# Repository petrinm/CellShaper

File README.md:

# CellShaper
The ultimate 18650 battery cell tester

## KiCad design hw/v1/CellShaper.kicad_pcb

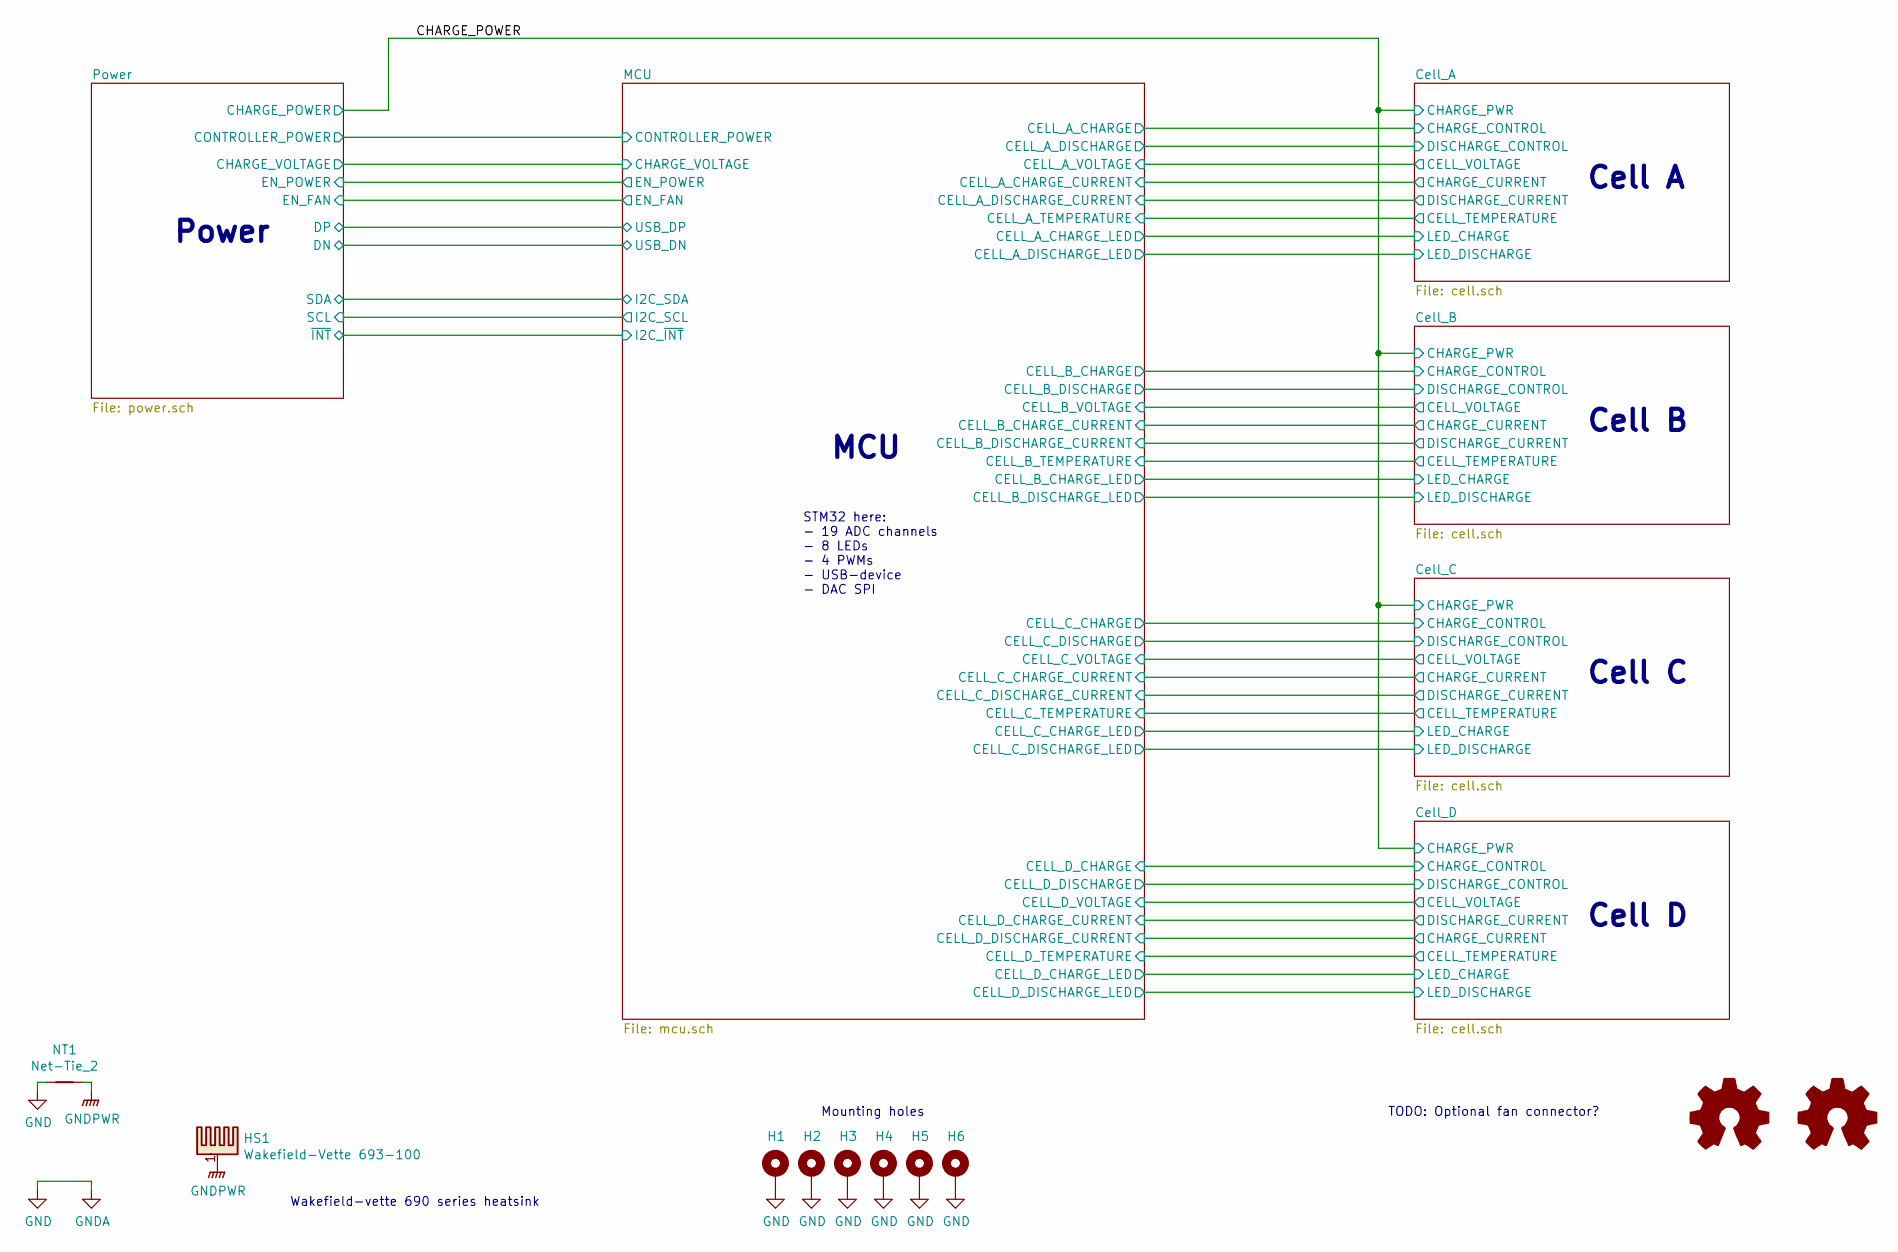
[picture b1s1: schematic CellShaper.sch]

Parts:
H1, H2, H3, H4, H5, H6: M3 hole; MountingHole_3.2mm_M3_Pad
HS1: Wakefield-Vette 693-100; Wakefield-vette_693-100
LOGO1: Logo_Open_Hardware_Small; OSHW-Logo_7.5x8mm_Copper
LOGO2: Logo_Open_Hardware_Small; OSHW-Logo_7.5x8mm_SilkScreen
NT1: Net-Tie_2; NetTie-2_SMD_Pad2.0mm

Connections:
GND: H1.1, H2.1, H3.1, H4.1, H5.1, H6.1, NT1.1; also elsewhere on the board
GNDPWR: HS1.1, NT1.2; also elsewhere on the board

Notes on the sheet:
Wakefield-vette 690 series heatsink
STM32 here: - 19 ADC channels - 8 LEDs - 4 PWMs - USB-device - DAC SPI
TODO: Optional fan connector?
Mounting holes
Cell A
Cell B
Cell D
Cell C
MCU
Power

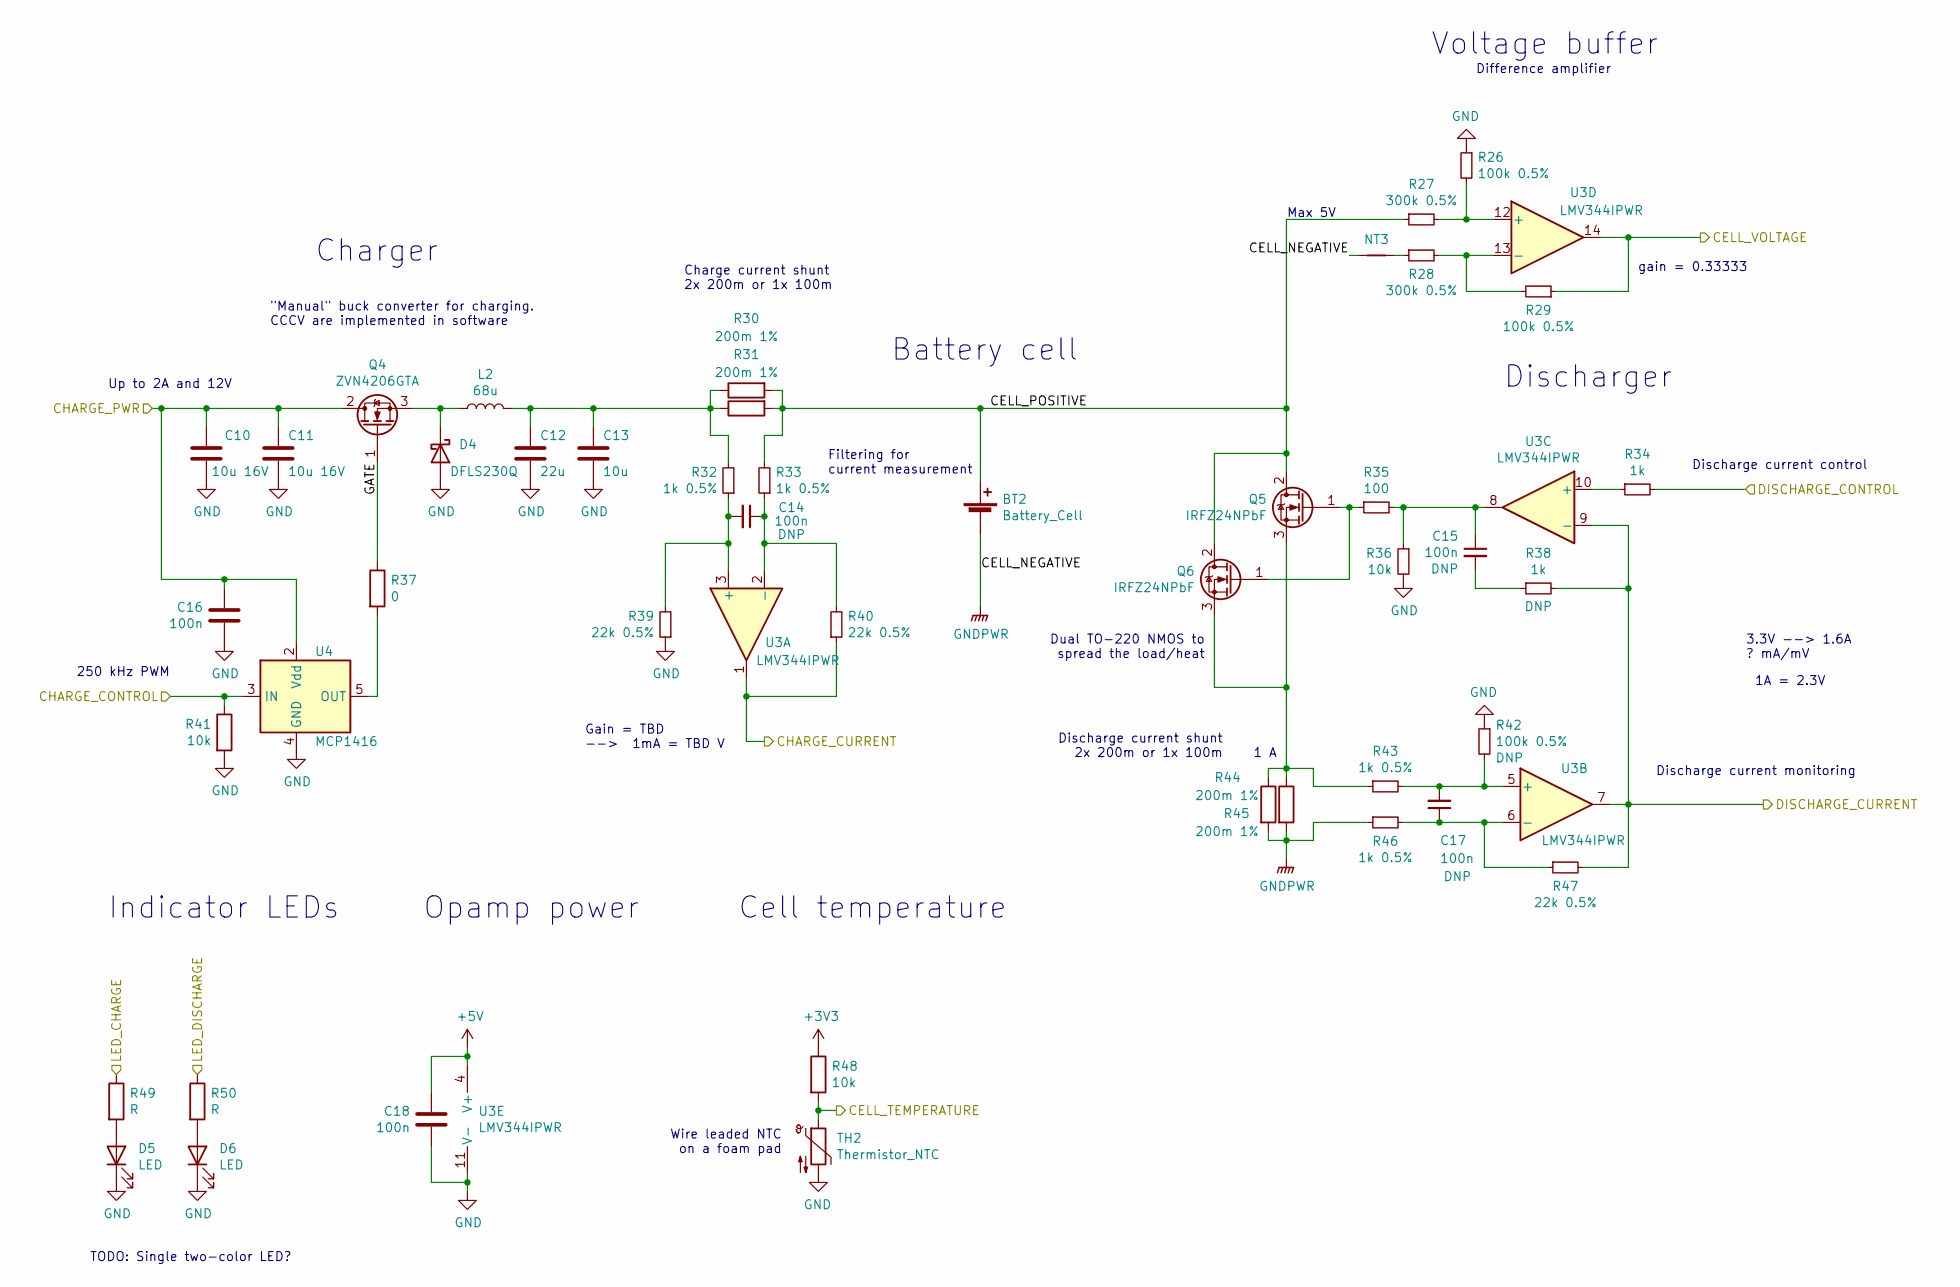
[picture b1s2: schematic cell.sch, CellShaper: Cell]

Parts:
BT1: Battery_Cell; BatteryHolder_Keystone_534_54
C1, C2: 10u 16V; C_0805_2012Metric
C3: 22u; C_0805_2012Metric
C4: 10u; C_0805_2012Metric
C5, C6, C7, C8, C9: 100n; C_0603_1608Metric
D1: DFLS230Q; D_PowerDI-123
D2, D3: LED; LED_0603_1608Metric
L1: 68u; L_Wuerth_HCM-1052
NT5: Net-Tie_2; NetTie-2_SMD_Pad0.5mm
Q1: ZVN4206GTA; SOT-223-3_TabPin2
Q2, Q3: IRFZ24NPbF; TO-220-3_Vertical
R1, R4, R17: 100k 0.5%; R_0603_1608Metric
R2, R3: 300k 0.5%; R_0603_1608Metric
R5, R6, R19, R20: 200m 1%; R_1206_3216Metric
R7, R8, R18, R21: 1k 0.5%; R_0603_1608Metric
R9, R13: 1k; R_0603_1608Metric
R10: 100; R_0603_1608Metric
R11, R16, R23: 10k; R_0603_1608Metric
R12: 0; R_0603_1608Metric
R14, R15, R22: 22k 0.5%; R_0603_1608Metric
R24, R25: R; R_0603_1608Metric
TH1: Thermistor_NTC; ContactThermistor
U1: LMV344IPWR; TSSOP-14_4.4x5mm_P0.65mm
U2: MCP1416; SOT-23-5

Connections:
+3V3: R23.1; also elsewhere on the board
+5V: C9.1, U1.4 (V+); also elsewhere on the board
/CHARGE_POWER: C1.1, C2.1, C7.1, Q1.2 (D), U2.2 (Vdd); also elsewhere on the board
/Cell_A/CELL_POSITIVE: BT1.1 (+), Q2.2 (D), Q3.2 (D), R2.1, R5.2, R6.2, R8.2
/Cell_A/GATE: Q1.1 (G), R12.1
/MCU/CELL_A_CHARGE: R16.1, U2.3 (IN); also elsewhere on the board
/MCU/CELL_A_CHARGE_CURRENT: R15.1, U1.1; also elsewhere on the board
/MCU/CELL_A_CHARGE_LED: R24.1; also elsewhere on the board
/MCU/CELL_A_DISCHARGE: R9.2; also elsewhere on the board
/MCU/CELL_A_DISCHARGE_CURRENT: R13.2, R22.2, U1.7, U1.9 (-); also elsewhere on the board
/MCU/CELL_A_DISCHARGE_LED: R25.1; also elsewhere on the board
/MCU/CELL_A_TEMPERATURE: R23.2, TH1.1; also elsewhere on the board
/MCU/CELL_A_VOLTAGE: R4.1, U1.14; also elsewhere on the board
GND: C1.2, C2.2, C3.2, C4.2, C7.2, C9.2, D1.2 (A), D2.1 (K), D3.1 (K), R1.1, R11.2, R14.1, R16.2, R17.1, TH1.2, U1.11 (V-), U2.4 (GND); also elsewhere on the board
GNDPWR: BT1.2 (-), NT5.1, R19.2, R20.2, R21.1; also elsewhere on the board
unnamed: C3.1, C4.1, L1.2, R5.1, R6.1, R7.2
unnamed: C5.1, R8.1, R15.2, U1.2 (-)
unnamed: C5.2, R7.1, R14.2, U1.3 (+)
unnamed: C6.1, R10.2, R11.1, U1.8
unnamed: C6.2, R13.1
unnamed: C8.1, R21.2, R22.1, U1.6 (-)
unnamed: C8.2, R17.2, R18.2, U1.5 (+)
unnamed: D1.1 (K), L1.1, Q1.3 (S)
unnamed: D2.2 (A), R24.2
unnamed: D3.2 (A), R25.2
unnamed: Q2.1 (G), Q3.1 (G), R10.1
unnamed: Q2.3 (S), Q3.3 (S), R18.1, R19.1, R20.1
unnamed: R1.2, R2.2, U1.12 (+)
unnamed: R3.2, R4.2, U1.13 (-)
unnamed: R9.1, U1.10 (+)
unnamed: R12.2, U2.5 (OUT)

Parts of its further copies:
BT2, BT3, BT4: Battery_Cell; BatteryHolder_Keystone_534_54
C10, C11, C19, C20, C28, C29: 10u 16V; C_0805_2012Metric
C12, C21, C30: 22u; C_0805_2012Metric
C13, C22, C31: 10u; C_0805_2012Metric
C14, C15, C16, C17, C18, C23, C24, C25, C26, C27, C32, C33, C34, C35, C36: 100n; C_0603_1608Metric
D4, D7, D10: DFLS230Q; D_PowerDI-123
D5, D6, D8, D9, D11, D12: LED; LED_0603_1608Metric
NT2, NT3, NT4: Net-Tie_2; NetTie-2_SMD_Pad0.5mm
Q4, Q7, Q10: ZVN4206GTA; SOT-223-3_TabPin2
Q5, Q6, Q8, Q9, Q11, Q12: IRFZ24NPbF; TO-220-3_Vertical
R26, R29, R42, R51, R54, R67, R76, R79, R92: 100k 0.5%; R_0603_1608Metric
R27, R28, R52, R53, R77, R78: 300k 0.5%; R_0603_1608Metric
R30, R31, R44, R45, R55, R56, R69, R70, R80, R81, R94, R95: 200m 1%; R_1206_3216Metric
R32, R33, R43, R46, R57, R58, R68, R71, R82, R83, R93, R96: 1k 0.5%; R_0603_1608Metric
R34, R38, R59, R63, R84, R88: 1k; R_0603_1608Metric
R35, R60, R85: 100; R_0603_1608Metric
R36, R41, R48, R61, R66, R73, R86, R91, R98: 10k; R_0603_1608Metric
R37, R62, R87: 0; R_0603_1608Metric
R39, R40, R47, R64, R65, R72, R89, R90, R97: 22k 0.5%; R_0603_1608Metric
R49, R50, R74, R75, R99, R100: R; R_0603_1608Metric
TH2, TH3, TH4: Thermistor_NTC; ContactThermistor
U3, U5, U7: LMV344IPWR; TSSOP-14_4.4x5mm_P0.65mm
U4, U6, U8: MCP1416; SOT-23-5

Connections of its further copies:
+3V3: R48.1, R73.1, R98.1; also elsewhere on the board
+5V: C18.1, C27.1, C36.1, U3.4 (V+), U5.4 (V+), U7.4 (V+); also elsewhere on the board
/CHARGE_POWER: C10.1, C11.1, C16.1, C19.1, C20.1, C25.1, C28.1, C29.1, C34.1, Q4.2 (D), Q7.2 (D), Q10.2 (D), U4.2 (Vdd), U6.2 (Vdd), U8.2 (Vdd); also elsewhere on the board
/Cell_B/CELL_POSITIVE: BT4.1 (+), Q11.2 (D), Q12.2 (D), R77.1, R80.2, R81.2, R83.2
/Cell_B/GATE: Q10.1 (G), R87.1
/Cell_C/CELL_POSITIVE: BT2.1 (+), Q5.2 (D), Q6.2 (D), R27.1, R30.2, R31.2, R33.2
/Cell_C/GATE: Q4.1 (G), R37.1
/Cell_D/CELL_POSITIVE: BT3.1 (+), Q8.2 (D), Q9.2 (D), R52.1, R55.2, R56.2, R58.2
/Cell_D/GATE: Q7.1 (G), R62.1
/MCU/CELL_B_CHARGE: R91.1, U8.3 (IN); also elsewhere on the board
/MCU/CELL_B_CHARGE_CURRENT: R90.1, U7.1; also elsewhere on the board
/MCU/CELL_B_CHARGE_LED: R99.1; also elsewhere on the board
/MCU/CELL_B_DISCHARGE: R84.2; also elsewhere on the board
/MCU/CELL_B_DISCHARGE_CURRENT: R88.2, R97.2, U7.7, U7.9 (-); also elsewhere on the board
/MCU/CELL_B_DISCHARGE_LED: R100.1; also elsewhere on the board
/MCU/CELL_B_TEMPERATURE: R98.2, TH4.1; also elsewhere on the board
/MCU/CELL_B_VOLTAGE: R79.1, U7.14; also elsewhere on the board
/MCU/CELL_C_CHARGE: R41.1, U4.3 (IN); also elsewhere on the board
/MCU/CELL_C_CHARGE_CURRENT: R40.1, U3.1; also elsewhere on the board
/MCU/CELL_C_CHARGE_LED: R49.1; also elsewhere on the board
/MCU/CELL_C_DISCHARGE: R34.2; also elsewhere on the board
/MCU/CELL_C_DISCHARGE_CURRENT: R38.2, R47.2, U3.7, U3.9 (-); also elsewhere on the board
/MCU/CELL_C_DISCHARGE_LED: R50.1; also elsewhere on the board
/MCU/CELL_C_TEMPERATURE: R48.2, TH2.1; also elsewhere on the board
/MCU/CELL_C_VOLTAGE: R29.1, U3.14; also elsewhere on the board
/MCU/CELL_D_CHARGE: R66.1, U6.3 (IN); also elsewhere on the board
/MCU/CELL_D_CHARGE_CURRENT: R63.2, R72.2, U5.7, U5.9 (-); also elsewhere on the board
/MCU/CELL_D_CHARGE_LED: R74.1; also elsewhere on the board
/MCU/CELL_D_DISCHARGE: R59.2; also elsewhere on the board
/MCU/CELL_D_DISCHARGE_CURRENT: R65.1, U5.1; also elsewhere on the board
/MCU/CELL_D_DISCHARGE_LED: R75.1; also elsewhere on the board
/MCU/CELL_D_TEMPERATURE: R73.2, TH3.1; also elsewhere on the board
/MCU/CELL_D_VOLTAGE: R54.1, U5.14; also elsewhere on the board
GND: C10.2, C11.2, C12.2, C13.2, C16.2, C18.2, C19.2, C20.2, C21.2, C22.2, C25.2, C27.2, C28.2, C29.2, C30.2, C31.2, C34.2, C36.2, D4.2 (A), D5.1 (K), D6.1 (K), D7.2 (A), D8.1 (K), D9.1 (K), D10.2 (A), D11.1 (K), D12.1 (K), R26.1, R36.2, R39.1, R41.2, R42.1, R51.1, R61.2, R64.1, R66.2, R67.1, R76.1, R86.2, R89.1, R91.2, R92.1, TH2.2, TH3.2, TH4.2, U3.11 (V-), U4.4 (GND), U5.11 (V-), U6.4 (GND), U7.11 (V-), U8.4 (GND); also elsewhere on the board
GNDPWR: BT2.2 (-), BT3.2 (-), BT4.2 (-), NT2.1, NT3.1, NT4.1, R44.2, R45.2, R46.1, R69.2, R70.2, R71.1, R94.2, R95.2, R96.1; also elsewhere on the board
unnamed 78: C12.1, C13.1, R30.1, R31.1, R32.2; also elsewhere on the board
unnamed: C14.1, R33.1, R40.2, U3.2 (-)
unnamed: C14.2, R32.1, R39.2, U3.3 (+)
unnamed: C15.1, R35.2, R36.1, U3.8
unnamed: C15.2, R38.1
unnamed: C17.1, R46.2, R47.1, U3.6 (-)
unnamed: C17.2, R42.2, R43.2, U3.5 (+)
unnamed 85: C21.1, C22.1, R55.1, R56.1, R57.2; also elsewhere on the board
unnamed: C23.1, R58.1, R65.2, U5.2 (-)
unnamed: C23.2, R57.1, R64.2, U5.3 (+)
unnamed: C24.1, R60.2, R61.1, U5.8
unnamed: C24.2, R63.1
unnamed: C26.1, R71.2, R72.1, U5.6 (-)
unnamed: C26.2, R67.2, R68.2, U5.5 (+)
unnamed 92: C30.1, C31.1, R80.1, R81.1, R82.2; also elsewhere on the board
unnamed: C32.1, R83.1, R90.2, U7.2 (-)
unnamed: C32.2, R82.1, R89.2, U7.3 (+)
unnamed: C33.1, R85.2, R86.1, U7.8
unnamed: C33.2, R88.1
unnamed: C35.1, R96.2, R97.1, U7.6 (-)
unnamed: C35.2, R92.2, R93.2, U7.5 (+)
unnamed 106: D4.1 (K), Q4.3 (S); also elsewhere on the board
unnamed: D5.2 (A), R49.2
unnamed: D6.2 (A), R50.2
unnamed 109: D7.1 (K), Q7.3 (S); also elsewhere on the board
unnamed: D8.2 (A), R74.2
unnamed: D9.2 (A), R75.2
unnamed 112: D10.1 (K), Q10.3 (S); also elsewhere on the board
unnamed: D11.2 (A), R99.2
unnamed: D12.2 (A), R100.2
unnamed: NT3.2, R28.1
unnamed: NT4.2, R53.1
unnamed: Q5.1 (G), Q6.1 (G), R35.1
unnamed: Q5.3 (S), Q6.3 (S), R43.1, R44.1, R45.1
unnamed: Q8.1 (G), Q9.1 (G), R60.1
unnamed: Q8.3 (S), Q9.3 (S), R68.1, R69.1, R70.1
unnamed: Q11.1 (G), Q12.1 (G), R85.1
unnamed: Q11.3 (S), Q12.3 (S), R93.1, R94.1, R95.1
unnamed: R26.2, R27.2, U3.12 (+)
unnamed: R28.2, R29.2, U3.13 (-)
unnamed: R34.1, U3.10 (+)
unnamed: R37.2, U4.5 (OUT)
unnamed: R51.2, R52.2, U5.12 (+)
unnamed: R53.2, R54.2, U5.13 (-)
unnamed: R59.1, U5.10 (+)
unnamed: R62.2, U6.5 (OUT)
unnamed: R76.2, R77.2, U7.12 (+)
unnamed: R78.2, R79.2, U7.13 (-)
unnamed: R84.1, U7.10 (+)
unnamed: R87.2, U8.5 (OUT)

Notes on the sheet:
1 A
Indicator LEDs
Discharger
Battery cell
Charger
Voltage buffer
250 kHz PWM
"Manual" buck converter for charging. CCCV are implemented in software
Charge current shunt 2x 200m or 1x 100m
Discharge current monitoring
Dual TO-220 NMOS to spread the load/heat
Filtering for current measurement
Gain = TBD --> 1mA = TBD V
Cell temperature
Opamp power
Up to 2A and 12V
Wire leaded NTC on a foam pad
TODO: Single two-color LED?
3.3V --> 1.6A ? mA/mV
Max 5V
1A = 2.3V
Difference amplifier
gain = 0.33333
Discharge current control
Discharge current shunt 2x 200m or 1x 100m

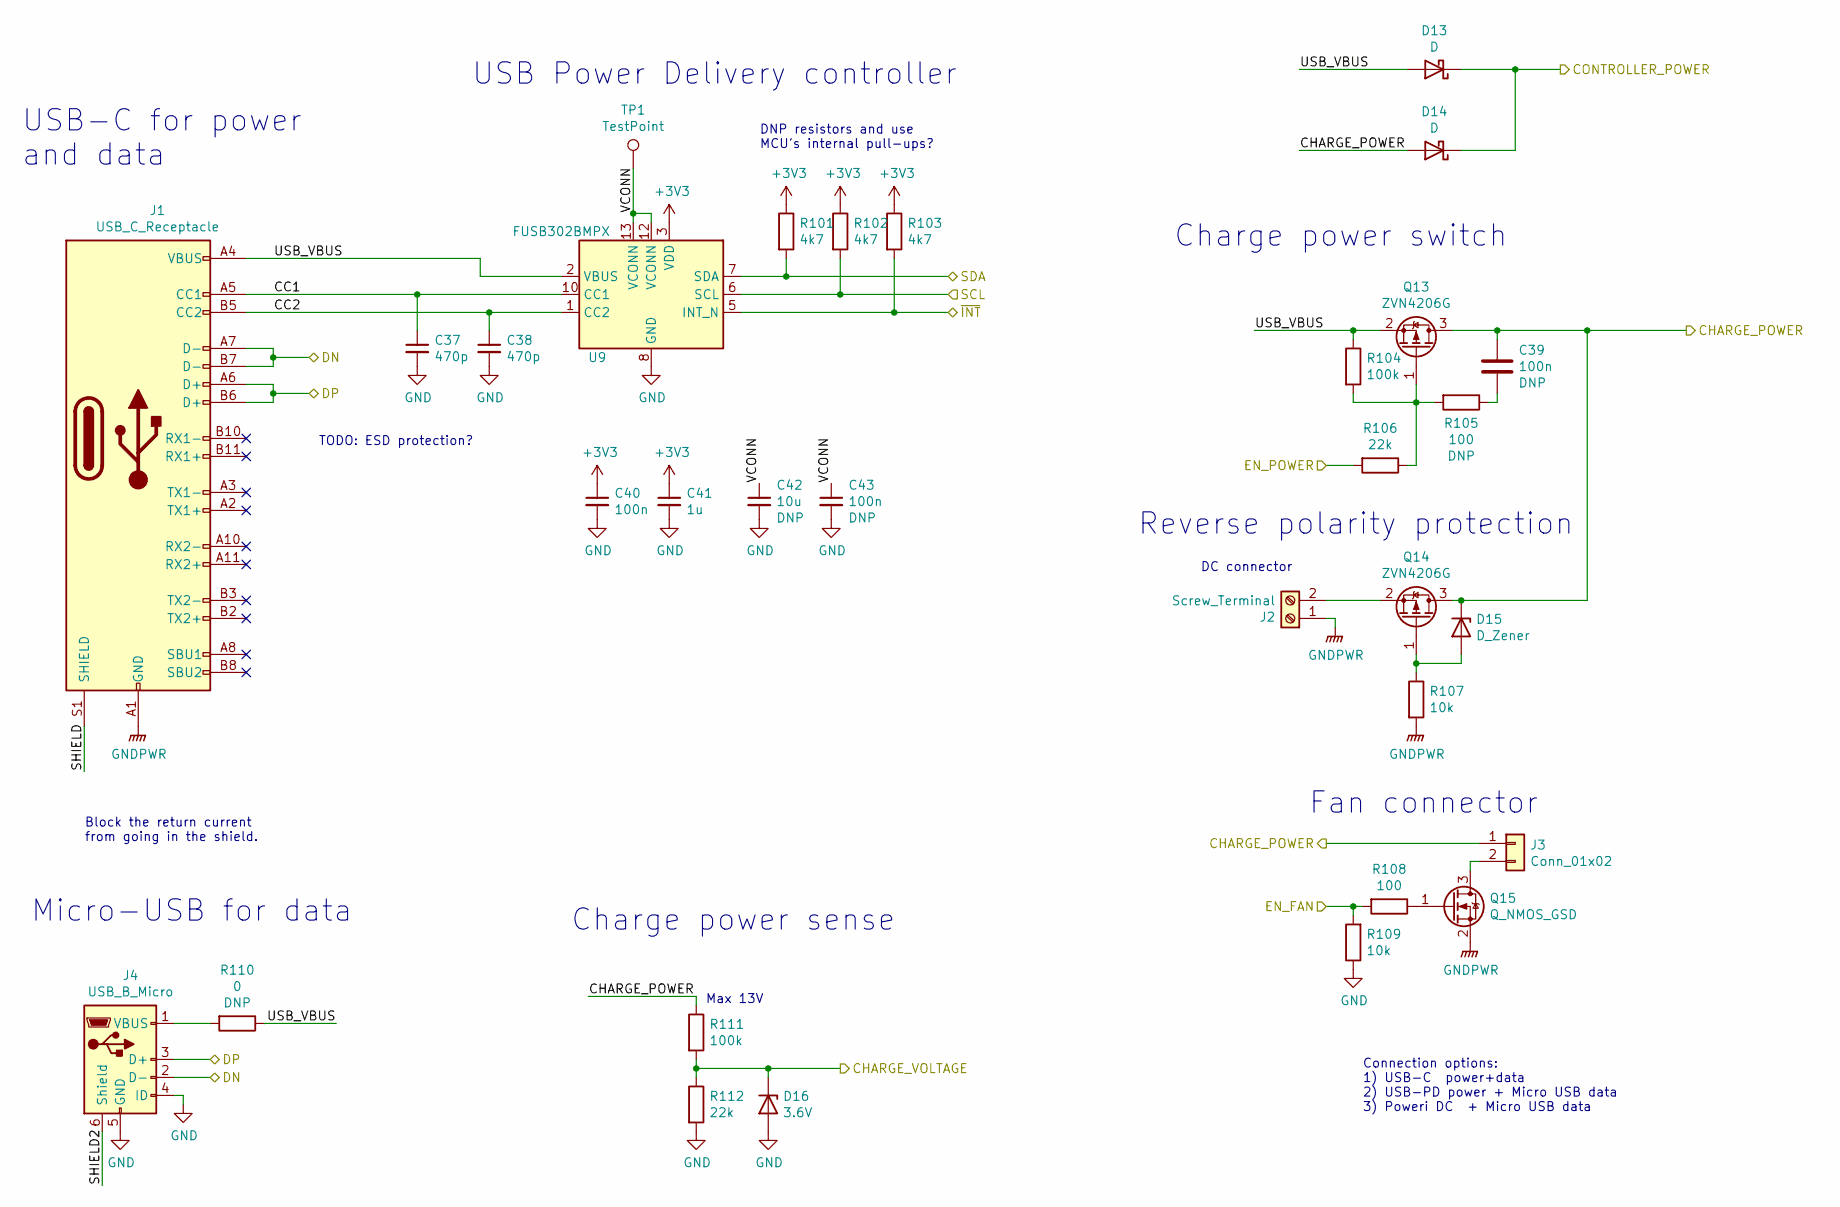
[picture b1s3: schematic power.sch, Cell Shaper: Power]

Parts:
C37, C38: 470p; C_0603_1608Metric
C39, C40, C43: 100n; C_0603_1608Metric
C41: 1u; C_0603_1608Metric
C42: 10u; C_0805_2012Metric
D13, D14: D; D_SOD-123
D15: D_Zener; D_SOD-123
D16: 3.6V; D_SOD-110
J1: USB_C_Receptacle; USB_C_Receptacle_Amphenol_12401610E4-2A
J2: Screw_Terminal; TerminalBlock_bornier-2_P5.08mm
J3: Conn_01x02; JST_EH_S2B-EH_1x02_P2.50mm_Horizontal
J4: USB_B_Micro; USB_Micro-B_GCT_USB3076-30-A
Q13, Q14: ZVN4206G; SOT-223-3_TabPin2
Q15: Q_NMOS_GSD; SOT-23
R101, R102, R103: 4k7; R_0603_1608Metric
R104, R111: 100k; R_0603_1608Metric
R105, R108: 100; R_0603_1608Metric
R106, R112: 22k; R_0603_1608Metric
R107, R109: 10k; R_0603_1608Metric
R110: 0; R_0603_1608Metric
TP1: TestPoint; TestPoint_Pad_D1.5mm
U9: FUSB302BMPX; WQFN-14-1EP_2.5x2.5mm_P0.5mm_EP1.45x1.45mm

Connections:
+3V3: C40.1, C41.1, R101.1, R102.1, R103.1, U9.3 (VDD), U9.4 (VDD); also elsewhere on the board
/CHARGE_POWER: C39.1, D14.2 (A), D15.1 (K), J3.1, Q13.3 (D), Q14.3 (D), R111.1; also elsewhere on the board
/MCU/CHARGE_VOLTAGE: D16.1 (K), R111.2, R112.1; also elsewhere on the board
/MCU/CONTROLLER_POWER: D13.1 (K), D14.1 (K); also elsewhere on the board
/MCU/EN_FAN: R108.2, R109.2; also elsewhere on the board
/MCU/EN_POWER: R106.2; also elsewhere on the board
/MCU/I2C_SCL: R102.2, U9.6 (SCL); also elsewhere on the board
/MCU/I2C_SDA: R101.2, U9.7 (SDA); also elsewhere on the board
/MCU/I2C_~INT: R103.2, U9.5 (INT_N); also elsewhere on the board
/Power/CC1: C37.1, J1.A5 (CC1), U9.10 (CC1), U9.11 (CC1)
/Power/CC2: C38.1, J1.B5 (CC2), U9.1 (CC2), U9.14 (CC2)
/Power/DN: J1.A7 (D-), J1.B7 (D-), J4.2 (D-); also elsewhere on the board
/Power/DP: J1.A6 (D+), J1.B6 (D+), J4.3 (D+); also elsewhere on the board
/Power/SHIELD: J1.S1 (SHIELD)
/Power/SHIELD2: J4.6 (Shield)
/Power/USB_VBUS: D13.2 (A), J1.A4 (VBUS), J1.A9 (VBUS), J1.B4 (VBUS), J1.B9 (VBUS), Q13.2 (S), R104.1, R110.1, U9.2 (VBUS)
/Power/VCONN: C42.1, C43.1, TP1.1, U9.12 (VCONN), U9.13 (VCONN)
GND: C37.2, C38.2, C40.2, C41.2, C42.2, C43.2, D16.2 (A), J4.4 (ID), J4.5 (GND), R109.1, R112.2, U9.8 (GND), U9.9 (GND), U9.15 (GND); also elsewhere on the board
GNDPWR: J1.A1 (GND), J1.A12 (GND), J1.B1 (GND), J1.B12 (GND), J2.1, Q15.2 (S), R107.2; also elsewhere on the board
unnamed: C39.2, R105.1
unnamed: D15.2 (A), Q14.1 (G), R107.1
unnamed: J2.2, Q14.2 (S)
unnamed: J3.2, Q15.3 (D)
unnamed: J4.1 (VBUS), R110.2
unnamed: Q13.1 (G), R104.2, R105.2, R106.1
unnamed: Q15.1 (G), R108.1

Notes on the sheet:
Max 13V
Reverse polarity protection
Charge power sense
USB Power Delivery controller
Connection options: 1) USB-C power+data 2) USB-PD power + Micro USB data 3) Poweri DC + Micro USB data
DNP resistors and use MCU's internal pull-ups?
Block the return current from going in the shield.
TODO: ESD protection?
Charge power switch
DC connector
Fan connector
Micro-USB for data
USB-C for power and data

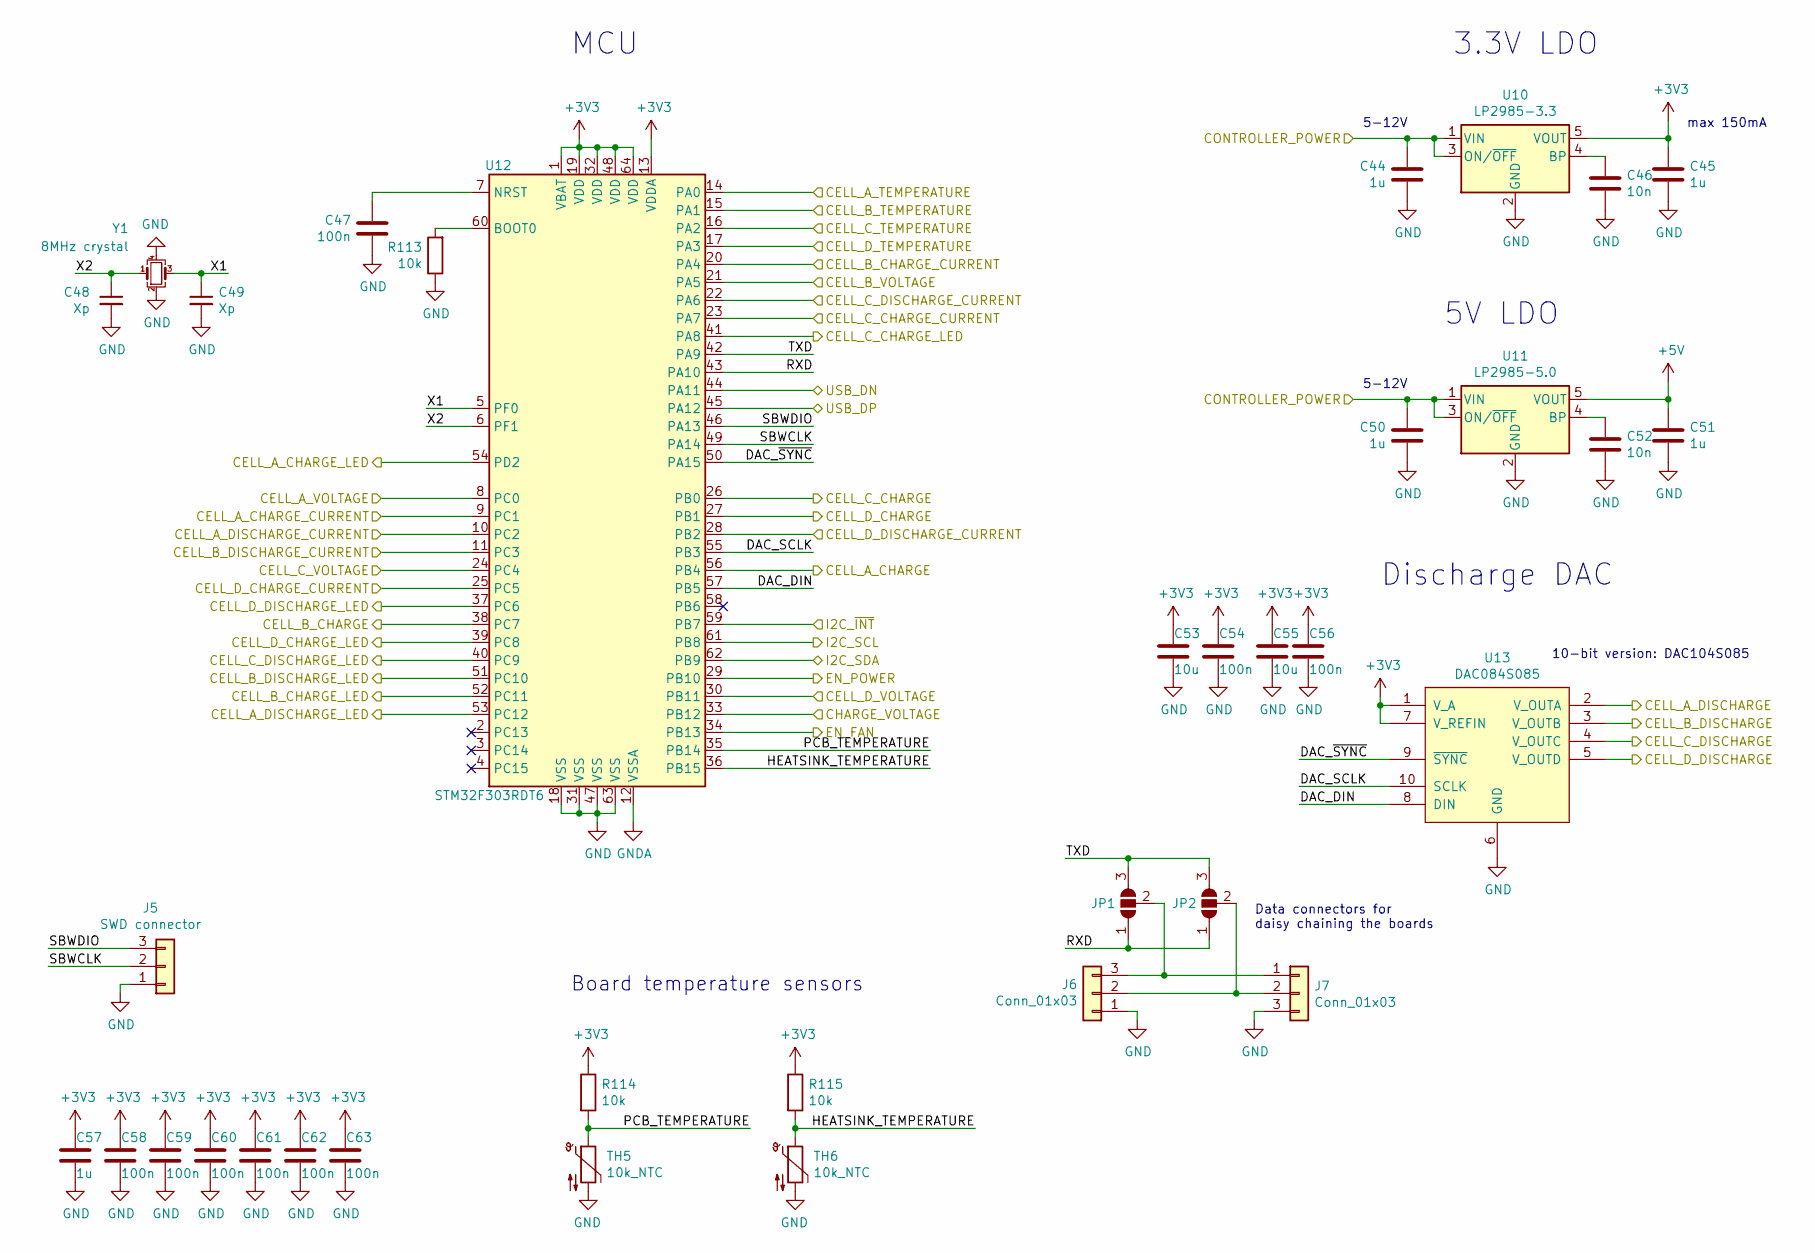
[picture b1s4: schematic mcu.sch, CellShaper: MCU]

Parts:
C44, C45, C50, C51, C57: 1u; C_0603_1608Metric
C46, C52: 10n; C_0603_1608Metric
C47, C54, C56, C58, C59, C60, C61, C62, C63: 100n; C_0603_1608Metric
C48, C49: Xp; C_0603_1608Metric
C53, C55: 10u; C_0805_2012Metric
J5: SWD connector; PinHeader_1x03_P2.54mm_Vertical
J6, J7: Conn_01x03; PinHeader_1x03_P2.54mm_Horizontal
JP1, JP2: SolderJumper_3_Open; SolderJumper-3_P1.3mm_Open_Pad1.0x1.5mm_NumberLabels
R113, R114, R115: 10k; R_0603_1608Metric
TH5: 10k_NTC; R_0603_1608Metric
TH6: 10k_NTC; PinHeader_1x02_P1.27mm_Vertical
U10: LP2985-3.3; SOT-23-5
U11: LP2985-5.0; SOT-23-5
U12: STM32F303RDT6; LQFP-64_10x10mm_P0.5mm
U13: DAC084S085; VSSOP-10_3x3mm_P0.5mm
Y1: 8MHz crystal; Crystal_SMD_Abracon_ABM8G-4Pin_3.2x2.5mm

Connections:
+3V3: C45.1, C53.2, C54.2, C55.2, C56.1, C57.1, C58.1, C59.1, C60.1, C61.1, C62.1, C63.1, R114.1, R115.1, U10.5 (VOUT), U12.1 (VBAT), U12.13 (VDDA), U12.19 (VDD), U12.32 (VDD), U12.48 (VDD), U12.64 (VDD), U13.1 (V_A), U13.7 (V_REFIN); also elsewhere on the board
+5V: C51.1, U11.5 (VOUT); also elsewhere on the board
/MCU/CELL_A_CHARGE: U12.56 (PB4); also elsewhere on the board
/MCU/CELL_A_CHARGE_CURRENT: U12.9 (PC1); also elsewhere on the board
/MCU/CELL_A_CHARGE_LED: U12.54 (PD2); also elsewhere on the board
/MCU/CELL_A_DISCHARGE: U13.2 (V_OUTA); also elsewhere on the board
/MCU/CELL_A_DISCHARGE_CURRENT: U12.10 (PC2); also elsewhere on the board
/MCU/CELL_A_DISCHARGE_LED: U12.53 (PC12); also elsewhere on the board
/MCU/CELL_A_TEMPERATURE: U12.14 (PA0); also elsewhere on the board
/MCU/CELL_A_VOLTAGE: U12.8 (PC0); also elsewhere on the board
/MCU/CELL_B_CHARGE: U12.38 (PC7); also elsewhere on the board
/MCU/CELL_B_CHARGE_CURRENT: U12.20 (PA4); also elsewhere on the board
/MCU/CELL_B_CHARGE_LED: U12.52 (PC11); also elsewhere on the board
/MCU/CELL_B_DISCHARGE: U13.3 (V_OUTB); also elsewhere on the board
/MCU/CELL_B_DISCHARGE_CURRENT: U12.11 (PC3); also elsewhere on the board
/MCU/CELL_B_DISCHARGE_LED: U12.51 (PC10); also elsewhere on the board
/MCU/CELL_B_TEMPERATURE: U12.15 (PA1); also elsewhere on the board
/MCU/CELL_B_VOLTAGE: U12.21 (PA5); also elsewhere on the board
/MCU/CELL_C_CHARGE: U12.26 (PB0); also elsewhere on the board
/MCU/CELL_C_CHARGE_CURRENT: U12.23 (PA7); also elsewhere on the board
/MCU/CELL_C_CHARGE_LED: U12.41 (PA8); also elsewhere on the board
/MCU/CELL_C_DISCHARGE: U13.4 (V_OUTC); also elsewhere on the board
/MCU/CELL_C_DISCHARGE_CURRENT: U12.22 (PA6); also elsewhere on the board
/MCU/CELL_C_DISCHARGE_LED: U12.40 (PC9); also elsewhere on the board
/MCU/CELL_C_TEMPERATURE: U12.16 (PA2); also elsewhere on the board
/MCU/CELL_C_VOLTAGE: U12.24 (PC4); also elsewhere on the board
/MCU/CELL_D_CHARGE: U12.27 (PB1); also elsewhere on the board
/MCU/CELL_D_CHARGE_CURRENT: U12.25 (PC5); also elsewhere on the board
/MCU/CELL_D_CHARGE_LED: U12.39 (PC8); also elsewhere on the board
/MCU/CELL_D_DISCHARGE: U13.5 (V_OUTD); also elsewhere on the board
/MCU/CELL_D_DISCHARGE_CURRENT: U12.28 (PB2); also elsewhere on the board
/MCU/CELL_D_DISCHARGE_LED: U12.37 (PC6); also elsewhere on the board
/MCU/CELL_D_TEMPERATURE: U12.17 (PA3); also elsewhere on the board
/MCU/CELL_D_VOLTAGE: U12.30 (PB11); also elsewhere on the board
/MCU/CHARGE_VOLTAGE: U12.33 (PB12); also elsewhere on the board
/MCU/CONTROLLER_POWER: C44.1, C50.1, U10.1 (VIN), U10.3 (ON/~OFF~), U11.1 (VIN), U11.3 (ON/~OFF~); also elsewhere on the board
/MCU/DAC_DIN: U12.57 (PB5), U13.8 (DIN)
/MCU/DAC_SCLK: U12.55 (PB3), U13.10 (SCLK)
/MCU/DAC_~SYNC: U12.50 (PA15), U13.9 (~SYNC)
/MCU/EN_FAN: U12.34 (PB13); also elsewhere on the board
/MCU/EN_POWER: U12.29 (PB10); also elsewhere on the board
/MCU/HEATSINK_TEMPERATURE: R115.2, TH6.1, U12.36 (PB15)
/MCU/I2C_SCL: U12.61 (PB8); also elsewhere on the board
/MCU/I2C_SDA: U12.62 (PB9); also elsewhere on the board
/MCU/I2C_~INT: U12.59 (PB7); also elsewhere on the board
/MCU/PCB_TEMPERATURE: R114.2, TH5.1, U12.35 (PB14)
/MCU/RXD: JP1.1 (A), JP2.1 (A), U12.43 (PA10)
/MCU/SBWCLK: J5.2, U12.49 (PA14)
/MCU/SBWDIO: J5.3, U12.46 (PA13)
/MCU/TXD: JP1.3 (B), JP2.3 (B), U12.42 (PA9)
/MCU/X1: C49.1, U12.5 (PF0), Y1.3
/MCU/X2: C48.1, U12.6 (PF1), Y1.1
/Power/DN: U12.44 (PA11); also elsewhere on the board
/Power/DP: U12.45 (PA12); also elsewhere on the board
GND: C44.2, C45.2, C46.2, C47.2, C48.2, C49.2, C50.2, C51.2, C52.2, C53.1, C54.1, C55.1, C56.2, C57.2, C58.2, C59.2, C60.2, C61.2, C62.2, C63.2, J5.1, J6.1, J7.3, R113.1, TH5.2, TH6.2, U10.2 (GND), U11.2 (GND), U12.12 (VSSA), U12.18 (VSS), U12.31 (VSS), U12.47 (VSS), U12.63 (VSS), U13.6 (GND), Y1.2, Y1.4; also elsewhere on the board
unnamed: C46.1, U10.4 (BP)
unnamed: C47.1, U12.7 (NRST)
unnamed: C52.1, U11.4 (BP)
unnamed: J6.2, J7.2, JP2.2 (C)
unnamed: J6.3, J7.1, JP1.2 (C)
unnamed: R113.2, U12.60 (BOOT0)

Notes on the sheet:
Data connectors for daisy chaining the boards
Board temperature sensors
10-bit version: DAC104S085
Discharge DAC
3.3V LDO
max 150mA
5-12V
5V LDO
MCU

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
